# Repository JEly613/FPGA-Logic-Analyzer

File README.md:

### See sims/ For Current Progress

## Concept:

Logic analyzer & oscilloscope with 4 digital channels and 2 analog channels processed with the Cmod A7 35-T FPGA board. The board uses a UART-USB bridge so the streaming rate is highly limited. 

The solution is to write incoming data to SRAM then slowly read it all off, giving a snapshot of input signal. Goal is to do this at 100MHz for digital input.

Currently designing analog front end for digital and analog channels. See sims and calculations for more details.

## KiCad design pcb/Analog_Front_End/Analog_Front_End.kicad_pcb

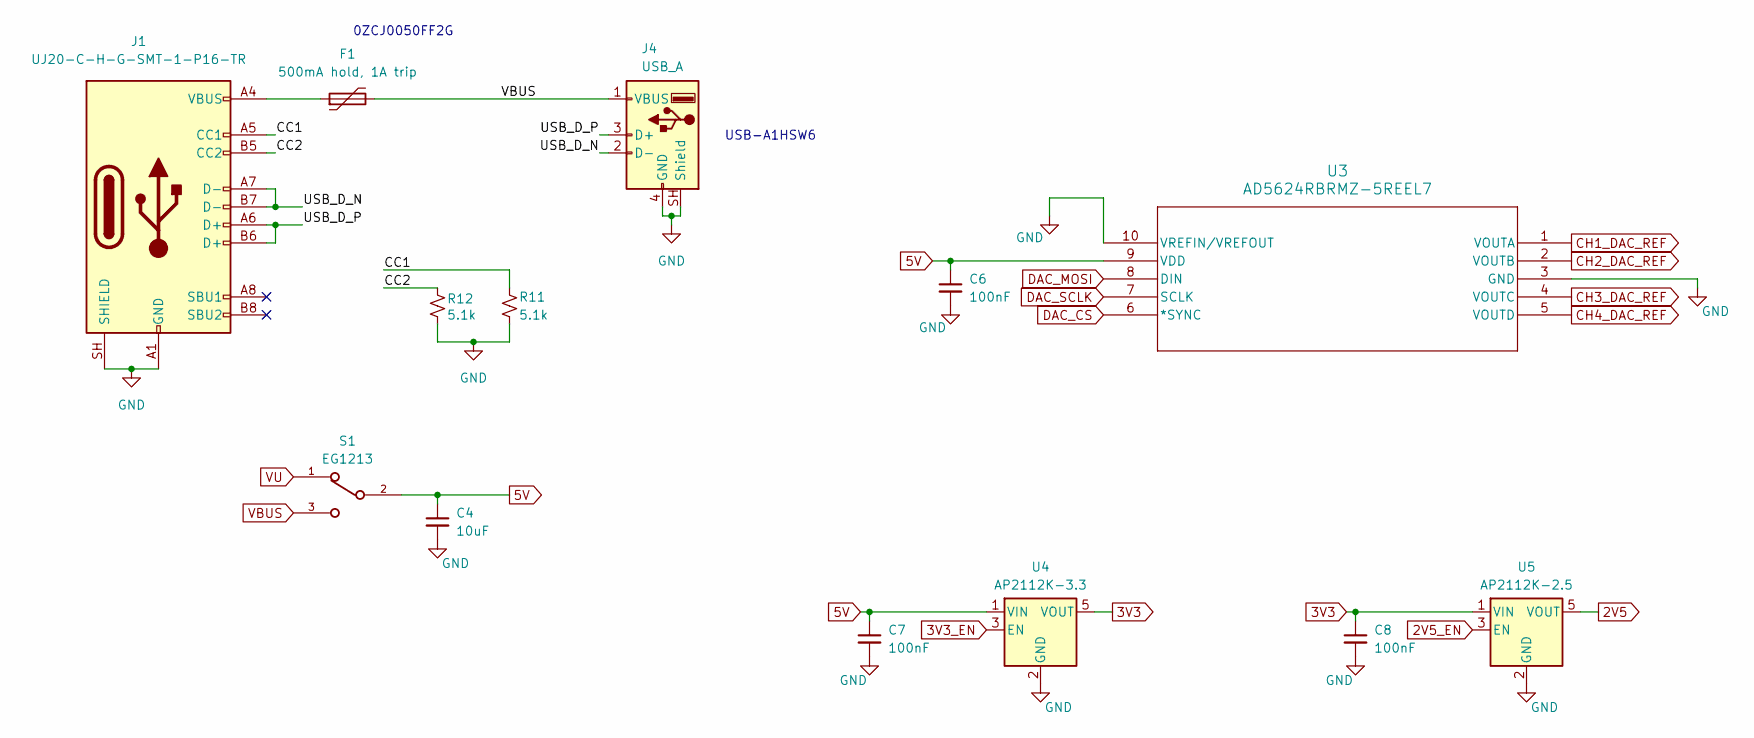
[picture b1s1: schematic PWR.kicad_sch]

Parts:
C4: 10uF; C_0603_1608Metric_Pad1.08x0.95mm_HandSolder
C6, C7, C8: 100nF; C_0603_1608Metric_Pad1.08x0.95mm_HandSolder
F1: 500mA hold, 1A trip; Fuse_1206_3216Metric_Pad1.42x1.75mm_HandSolder
J1: UJ20-C-H-G-SMT-1-P16-TR; SAMESKY_UJ20-C-H-G-SMT-1-P16-TR
J4: USB_A; CONN_USB-A1HSW6_OST
R11, R12: 5.1k; R_0603_1608Metric_Pad0.98x0.95mm_HandSolder
S1: EG1213; SW_EG1213; DigiKey_Part_Number EG1906-ND
U3: AD5624RBRMZ-5REEL7; RM_10_ADI-L
U4: AP2112K-3.3; SOT-23-5
U5: AP2112K-2.5; SOT-23-5

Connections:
2V5: U5.5 (VOUT); also elsewhere on the board
2V5_EN: U5.3 (EN); also elsewhere on the board
3V3: C8.1, U4.5 (VOUT), U5.1 (VIN); also elsewhere on the board
3V3_EN: U4.3 (EN); also elsewhere on the board
5V: C4.1, C6.1, C7.1, S1.2, U3.9 (VDD), U4.1 (VIN); also elsewhere on the board
/PWR/CC1: J1.A5 (CC1), R11.2
/PWR/CC2: J1.B5 (CC2), R12.2
/PWR/USB_D_N: J1.A7 (D-), J1.B7 (D-), J4.2 (D-)
/PWR/USB_D_P: J1.A6 (D+), J1.B6 (D+), J4.3 (D+)
CH1_DAC_REF: U3.1 (VOUTA); also elsewhere on the board
CH2_DAC_REF: U3.2 (VOUTB); also elsewhere on the board
CH3_DAC_REF: U3.4 (VOUTC); also elsewhere on the board
CH4_DAC_REF: U3.5 (VOUTD); also elsewhere on the board
DAC_CS: U3.6 (*SYNC); also elsewhere on the board
DAC_MOSI: U3.8 (DIN); also elsewhere on the board
DAC_SCLK: U3.7 (SCLK); also elsewhere on the board
GND: C4.2, C6.2, C7.2, C8.2, J1.A1 (GND), J1.A12 (GND), J1.B1 (GND), J1.B12 (GND), J1.SH (SHIELD), J4.4 (GND), J4.SH (Shield), R11.1, R12.1, U3.3 (GND), U3.10 (VREFIN/VREFOUT), U4.2 (GND), U5.2 (GND); also elsewhere on the board
unnamed: F1.1, J1.A4 (VBUS), J1.A9 (VBUS), J1.B4 (VBUS), J1.B9 (VBUS)
VBUS: F1.2, J4.1 (VBUS), S1.3
VU: S1.1; also elsewhere on the board

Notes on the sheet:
0ZCJ0050FF2G
USB-A1HSW6

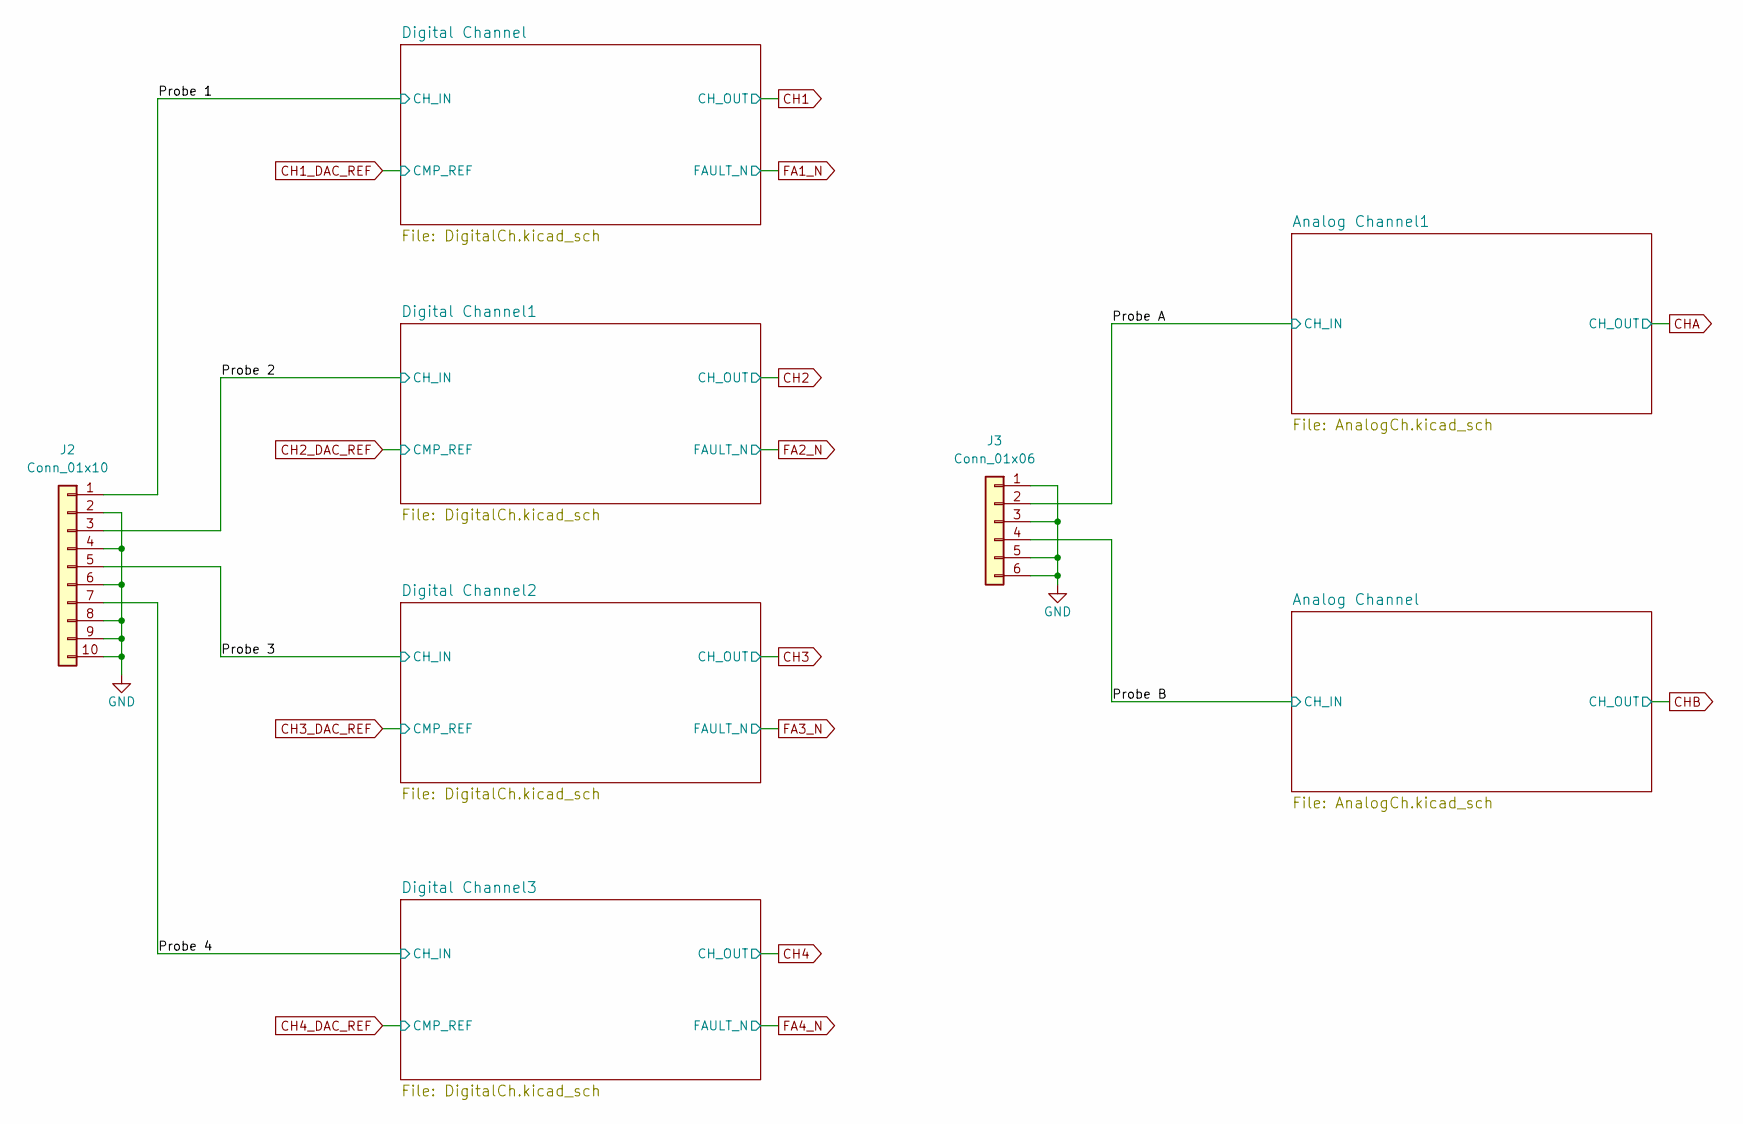
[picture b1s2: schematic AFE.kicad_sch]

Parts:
J2: Conn_01x10; BoxHeader_2x05_P2.54mm_Horizontal
J3: Conn_01x06; BoxHeader_2x03_P2.54mm_Horizontal

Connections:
/AFE/Probe 1: J2.1; also elsewhere on the board
/AFE/Probe 2: J2.3; also elsewhere on the board
/AFE/Probe 3: J2.5; also elsewhere on the board
/AFE/Probe 4: J2.7; also elsewhere on the board
/AFE/Probe A: J3.2; also elsewhere on the board
/AFE/Probe B: J3.4; also elsewhere on the board
GND: J2.2, J2.4, J2.6, J2.8, J2.9, J2.10, J3.1, J3.3, J3.5, J3.6; also elsewhere on the board

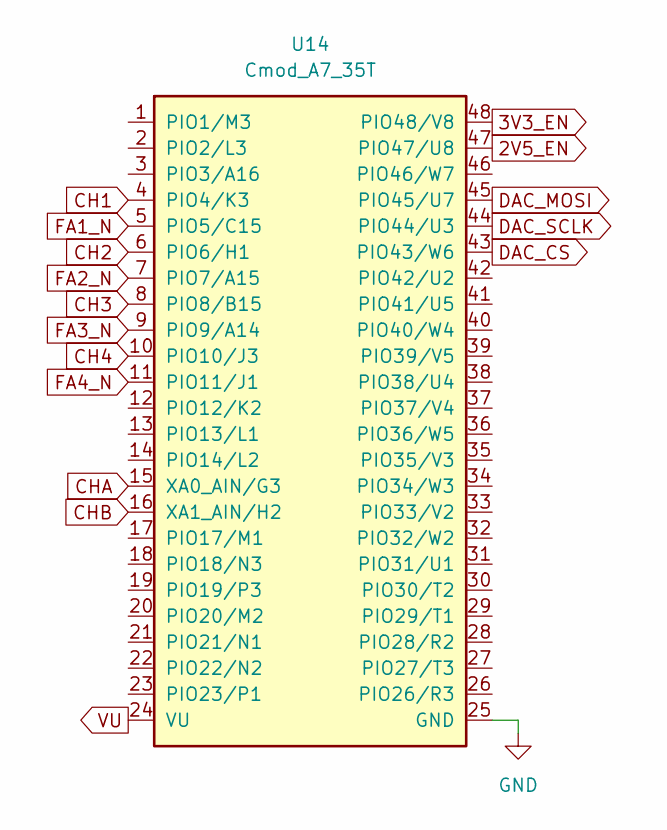
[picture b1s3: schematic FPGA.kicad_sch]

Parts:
U14: Cmod_A7_35T; Cmod_A7_DIP48_W15.24mm_Socket; MPN 410-328-35

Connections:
2V5_EN: U14.47 (PIO47/U8); also elsewhere on the board
3V3_EN: U14.48 (PIO48/V8); also elsewhere on the board
CH1: U14.4 (PIO4/K3); also elsewhere on the board
CH2: U14.6 (PIO6/H1); also elsewhere on the board
CH3: U14.8 (PIO8/B15); also elsewhere on the board
CH4: U14.10 (PIO10/J3); also elsewhere on the board
CHA: U14.15 (XA0_AIN/G3); also elsewhere on the board
CHB: U14.16 (XA1_AIN/H2); also elsewhere on the board
DAC_CS: U14.43 (PIO43/W6); also elsewhere on the board
DAC_MOSI: U14.45 (PIO45/U7); also elsewhere on the board
DAC_SCLK: U14.44 (PIO44/U3); also elsewhere on the board
FA1_N: U14.5 (PIO5/C15); also elsewhere on the board
FA2_N: U14.7 (PIO7/A15); also elsewhere on the board
FA3_N: U14.9 (PIO9/A14); also elsewhere on the board
FA4_N: U14.11 (PIO11/J1); also elsewhere on the board
GND: U14.25 (GND); also elsewhere on the board
VU: U14.24 (VU); also elsewhere on the board

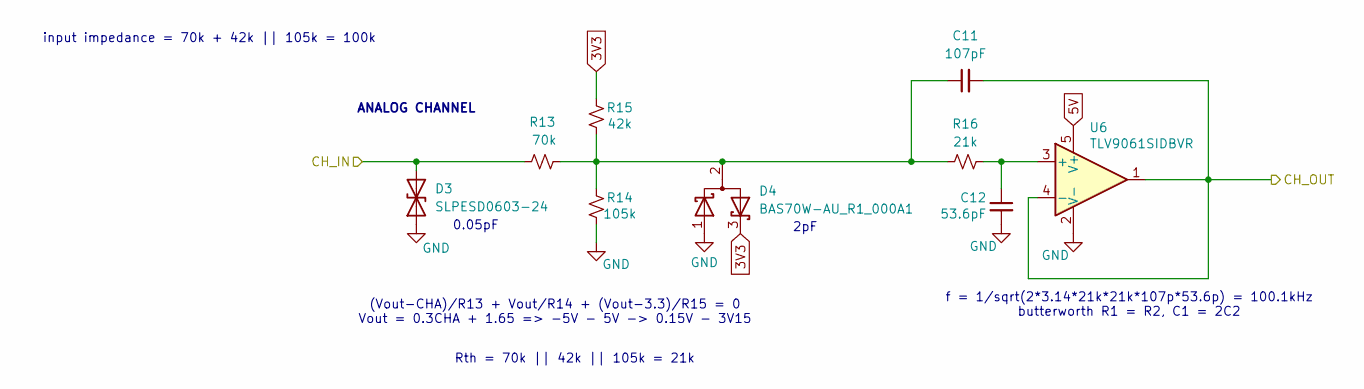
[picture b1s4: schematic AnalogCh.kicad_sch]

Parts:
C11: 107pF; C_0603_1608Metric_Pad1.08x0.95mm_HandSolder
C12: 53.6pF; C_0603_1608Metric_Pad1.08x0.95mm_HandSolder
D3: SLPESD0603-24; D_0603_1608Metric_Pad1.05x0.95mm_HandSolder
D4: BAS70W-AU_R1_000A1; SOT-323_SC-70
R13: 70k; R_0603_1608Metric_Pad0.98x0.95mm_HandSolder
R14: 105k; R_0603_1608Metric_Pad0.98x0.95mm_HandSolder
R15: 42k; R_0603_1608Metric_Pad0.98x0.95mm_HandSolder
R16: 21k; R_0603_1608Metric_Pad0.98x0.95mm_HandSolder
U6: TLV9061SIDBVR; SOT-23-5

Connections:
3V3: D4.3 (K), R15.1; also elsewhere on the board
5V: U6.5 (V+); also elsewhere on the board
/AFE/Probe B: D3.2 (A2), R13.1; also elsewhere on the board
CHB: C11.2, U6.1, U6.4 (-); also elsewhere on the board
GND: C12.2, D3.1 (A1), D4.1 (K), R14.2, U6.2 (V-); also elsewhere on the board
unnamed: C11.1, D4.2 (A), R13.2, R14.1, R15.2, R16.1
unnamed: C12.1, R16.2, U6.3 (+)

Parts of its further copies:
C23: 107pF; C_0603_1608Metric_Pad1.08x0.95mm_HandSolder
C24: 53.6pF; C_0603_1608Metric_Pad1.08x0.95mm_HandSolder
D11: SLPESD0603-24; D_0603_1608Metric_Pad1.05x0.95mm_HandSolder
D12: BAS70W-AU_R1_000A1; SOT-323_SC-70
R47: 70k; R_0603_1608Metric_Pad0.98x0.95mm_HandSolder
R48: 42k; R_0603_1608Metric_Pad0.98x0.95mm_HandSolder
R49: 105k; R_0603_1608Metric_Pad0.98x0.95mm_HandSolder
R50: 21k; R_0603_1608Metric_Pad0.98x0.95mm_HandSolder
U13: TLV9061SIDBVR; SOT-23-5

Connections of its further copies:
3V3: D12.3 (K), R48.1; also elsewhere on the board
5V: U13.5 (V+); also elsewhere on the board
/AFE/Probe A: D11.2 (A2), R47.1; also elsewhere on the board
CHA: C23.2, U13.1, U13.4 (-); also elsewhere on the board
GND: C24.2, D11.1 (A1), D12.1 (K), R49.2, U13.2 (V-); also elsewhere on the board
unnamed: C23.1, D12.2 (A), R47.2, R48.2, R49.1, R50.1
unnamed: C24.1, R50.2, U13.3 (+)

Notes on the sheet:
Rth = 70k || 42k || 105k = 21k
ANALOG CHANNEL
2pF
0.05pF
f = 1/sqrt(2*3.14*21k*21k*107p*53.6p) = 100.1kHz butterworth R1 = R2, C1 = 2C2
(Vout-CHA)/R13 + Vout/R14 + (Vout-3.3)/R15 = 0 Vout = 0.3CHA + 1.65 => -5V - 5V -> 0.15V - 3V15
input impedance = 70k + 42k || 105k = 100k

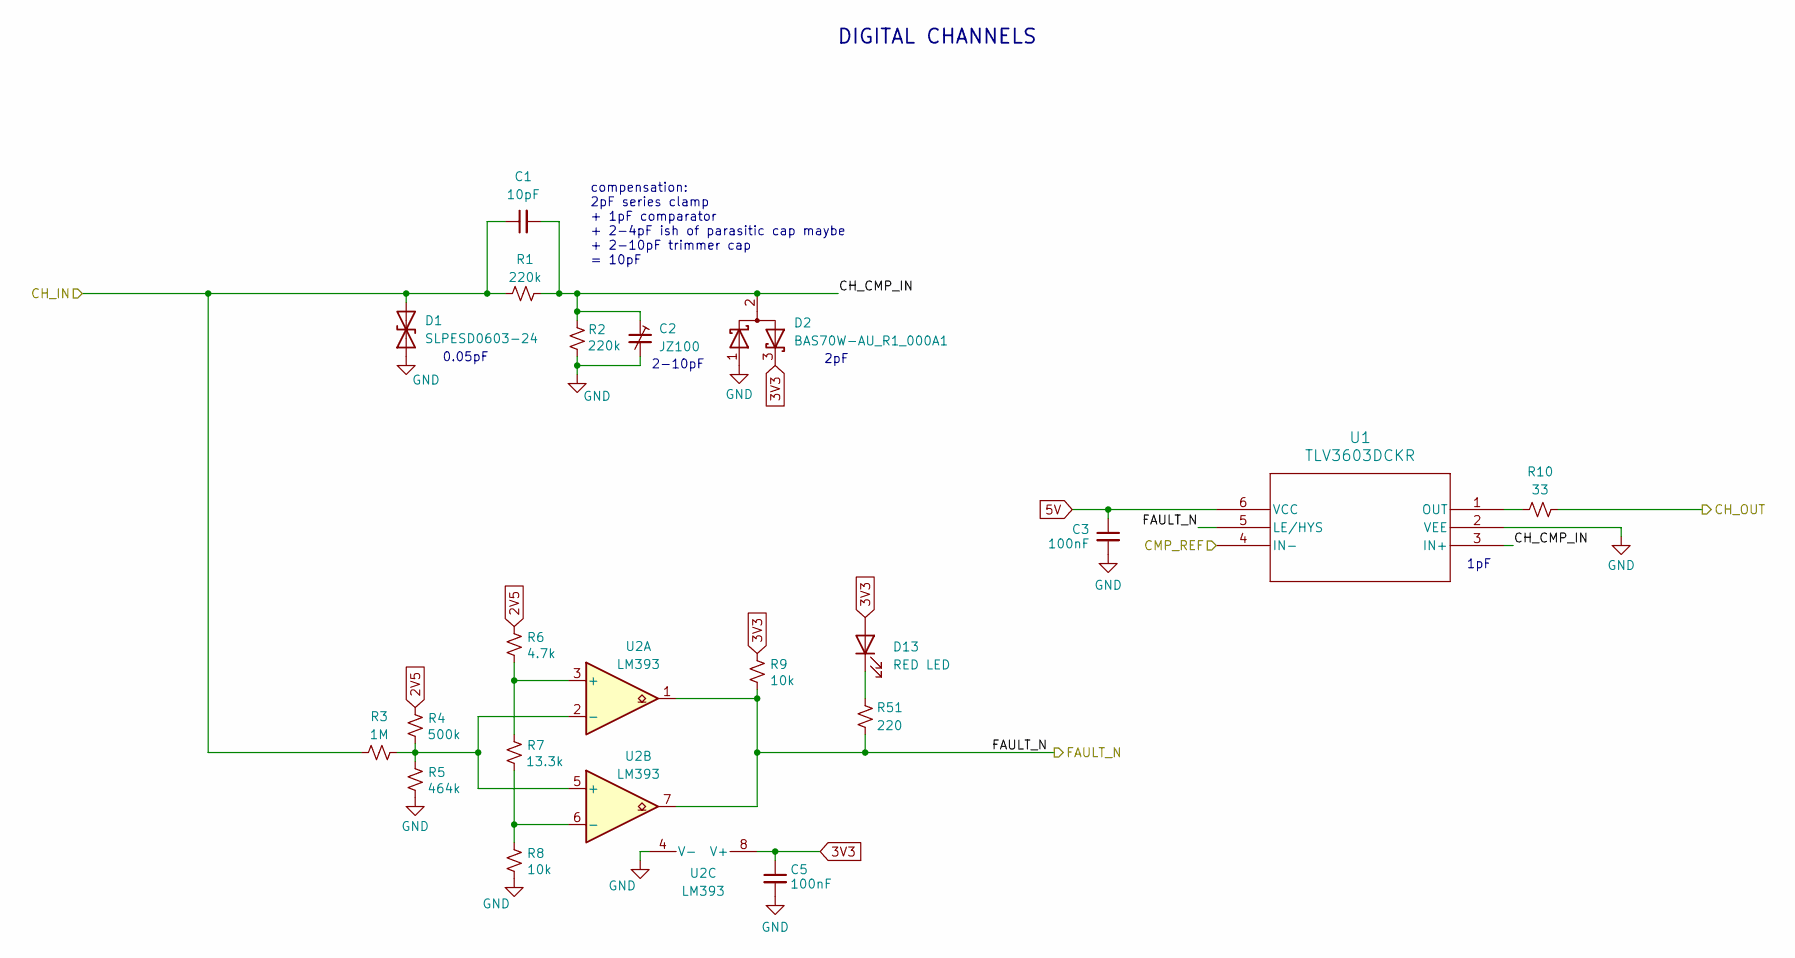
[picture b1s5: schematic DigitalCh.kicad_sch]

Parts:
C1: 10pF; C_0603_1608Metric_Pad1.08x0.95mm_HandSolder
C2: JZ100; C_0603_1608Metric_Pad1.08x0.95mm_HandSolder
C3, C5: 100nF; C_0603_1608Metric_Pad1.08x0.95mm_HandSolder
D1: SLPESD0603-24; D_0603_1608Metric_Pad1.05x0.95mm_HandSolder
D2: BAS70W-AU_R1_000A1; SOT-323_SC-70
D13: RED LED; LED_0805_2012Metric_Pad1.15x1.40mm_HandSolder
R1, R2: 220k; R_0603_1608Metric_Pad0.98x0.95mm_HandSolder
R3: 1M; R_0603_1608Metric_Pad0.98x0.95mm_HandSolder
R4: 500k; R_0603_1608Metric_Pad0.98x0.95mm_HandSolder
R5: 464k; R_0603_1608Metric_Pad0.98x0.95mm_HandSolder
R6: 4.7k; R_0603_1608Metric_Pad0.98x0.95mm_HandSolder
R7: 13.3k; R_0603_1608Metric_Pad0.98x0.95mm_HandSolder
R8, R9: 10k; R_0603_1608Metric_Pad0.98x0.95mm_HandSolder
R10: 33; R_0603_1608Metric_Pad0.98x0.95mm_HandSolder
R51: 220; R_0603_1608Metric_Pad0.98x0.95mm_HandSolder
U1: TLV3603DCKR; SC70_DCK_TEX
U2: LM393; LM393-L

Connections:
2V5: R4.1, R6.1; also elsewhere on the board
3V3: C5.1, D2.3 (K), D13.2 (A), R9.1, U2.8 (V+); also elsewhere on the board
5V: C3.1, U1.6 (VCC); also elsewhere on the board
/AFE/Digital Channel/CH_CMP_IN: C1.2, C2.1, D2.2 (A), R1.2, R2.1, U1.3 (IN+)
/AFE/Probe 1: C1.1, D1.2 (A2), R1.1, R3.1; also elsewhere on the board
CH1: R10.2; also elsewhere on the board
CH1_DAC_REF: U1.4 (IN-); also elsewhere on the board
FA1_N: R9.2, R51.2, U1.5 (LE/HYS), U2.1, U2.7; also elsewhere on the board
GND: C2.2, C3.2, C5.2, D1.1 (A1), D2.1 (K), R2.2, R5.2, R8.2, U1.2 (VEE), U2.4 (V-); also elsewhere on the board
unnamed: D13.1 (K), R51.1
unnamed: R10.1, U1.1 (OUT)
unnamed: R6.2, R7.1, U2.3 (+)
unnamed: R3.2, R4.2, R5.1, U2.2 (-), U2.5 (+)
unnamed: R7.2, R8.1, U2.6 (-)

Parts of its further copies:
C9, C15, C19: 10pF; C_0603_1608Metric_Pad1.08x0.95mm_HandSolder
C10, C16, C20: JZ100; C_0603_1608Metric_Pad1.08x0.95mm_HandSolder
C13, C14, C17, C18, C21, C22: 100nF; C_0603_1608Metric_Pad1.08x0.95mm_HandSolder
D5, D7, D9: SLPESD0603-24; D_0603_1608Metric_Pad1.05x0.95mm_HandSolder
D6, D8, D10: BAS70W-AU_R1_000A1; SOT-323_SC-70
D14, D15, D16: RED LED; LED_0805_2012Metric_Pad1.15x1.40mm_HandSolder
R17, R27, R37: 1M; R_0603_1608Metric_Pad0.98x0.95mm_HandSolder
R18, R28, R38: 500k; R_0603_1608Metric_Pad0.98x0.95mm_HandSolder
R19, R29, R39: 464k; R_0603_1608Metric_Pad0.98x0.95mm_HandSolder
R20, R30, R40: 4.7k; R_0603_1608Metric_Pad0.98x0.95mm_HandSolder
R21, R31, R41: 13.3k; R_0603_1608Metric_Pad0.98x0.95mm_HandSolder
R22, R25, R32, R35, R42, R45: 10k; R_0603_1608Metric_Pad0.98x0.95mm_HandSolder
R23, R24, R33, R34, R43, R44: 220k; R_0603_1608Metric_Pad0.98x0.95mm_HandSolder
R26, R36, R46: 33; R_0603_1608Metric_Pad0.98x0.95mm_HandSolder
R52, R53, R54: 220; R_0603_1608Metric_Pad0.98x0.95mm_HandSolder
U7, U9, U11: LM393; LM393-L
U8, U10, U12: TLV3603DCKR; SC70_DCK_TEX

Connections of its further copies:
2V5: R18.1, R20.1, R28.1, R30.1, R38.1, R40.1; also elsewhere on the board
3V3: C13.1, C17.1, C21.1, D6.3 (K), D8.3 (K), D10.3 (K), D14.2 (A), D15.2 (A), D16.2 (A), R25.1, R35.1, R45.1, U7.8 (V+), U9.8 (V+), U11.8 (V+); also elsewhere on the board
5V: C14.1, C18.1, C22.1, U8.6 (VCC), U10.6 (VCC), U12.6 (VCC); also elsewhere on the board
/AFE/Digital Channel1/CH_CMP_IN: C9.2, C10.1, D6.2 (A), R23.2, R24.1, U8.3 (IN+)
/AFE/Digital Channel2/CH_CMP_IN: C15.2, C16.1, D8.2 (A), R33.2, R34.1, U10.3 (IN+)
/AFE/Digital Channel3/CH_CMP_IN: C19.2, C20.1, D10.2 (A), R43.2, R44.1, U12.3 (IN+)
/AFE/Probe 2: C9.1, D5.2 (A2), R17.1, R23.1; also elsewhere on the board
/AFE/Probe 3: C15.1, D7.2 (A2), R27.1, R33.1; also elsewhere on the board
/AFE/Probe 4: C19.1, D9.2 (A2), R37.1, R43.1; also elsewhere on the board
CH2: R26.2; also elsewhere on the board
CH2_DAC_REF: U8.4 (IN-); also elsewhere on the board
CH3: R36.2; also elsewhere on the board
CH3_DAC_REF: U10.4 (IN-); also elsewhere on the board
CH4: R46.2; also elsewhere on the board
CH4_DAC_REF: U12.4 (IN-); also elsewhere on the board
FA2_N: R25.2, R52.2, U7.1, U7.7, U8.5 (LE/HYS); also elsewhere on the board
FA3_N: R35.2, R53.2, U9.1, U9.7, U10.5 (LE/HYS); also elsewhere on the board
FA4_N: R45.2, R54.2, U11.1, U11.7, U12.5 (LE/HYS); also elsewhere on the board
GND: C10.2, C13.2, C14.2, C16.2, C17.2, C18.2, C20.2, C21.2, C22.2, D5.1 (A1), D6.1 (K), D7.1 (A1), D8.1 (K), D9.1 (A1), D10.1 (K), R19.2, R22.2, R24.2, R29.2, R32.2, R34.2, R39.2, R42.2, R44.2, U7.4 (V-), U8.2 (VEE), U9.4 (V-), U10.2 (VEE), U11.4 (V-), U12.2 (VEE); also elsewhere on the board
unnamed: D14.1 (K), R52.1
unnamed: D15.1 (K), R53.1
unnamed: D16.1 (K), R54.1
unnamed: R20.2, R21.1, U7.3 (+)
unnamed: R17.2, R18.2, R19.1, U7.2 (-), U7.5 (+)
unnamed: R21.2, R22.1, U7.6 (-)
unnamed: R26.1, U8.1 (OUT)
unnamed: R30.2, R31.1, U9.3 (+)
unnamed: R27.2, R28.2, R29.1, U9.2 (-), U9.5 (+)
unnamed: R31.2, R32.1, U9.6 (-)
unnamed: R36.1, U10.1 (OUT)
unnamed: R40.2, R41.1, U11.3 (+)
unnamed: R37.2, R38.2, R39.1, U11.2 (-), U11.5 (+)
unnamed: R41.2, R42.1, U11.6 (-)
unnamed: R46.1, U12.1 (OUT)

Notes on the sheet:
1pF
0.05pF
2pF
DIGITAL CHANNELS
compensation: 2pF series clamp + 1pF comparator + 2-4pF ish of parasitic cap maybe + 2-10pF trimmer cap = 10pF
2-10pF

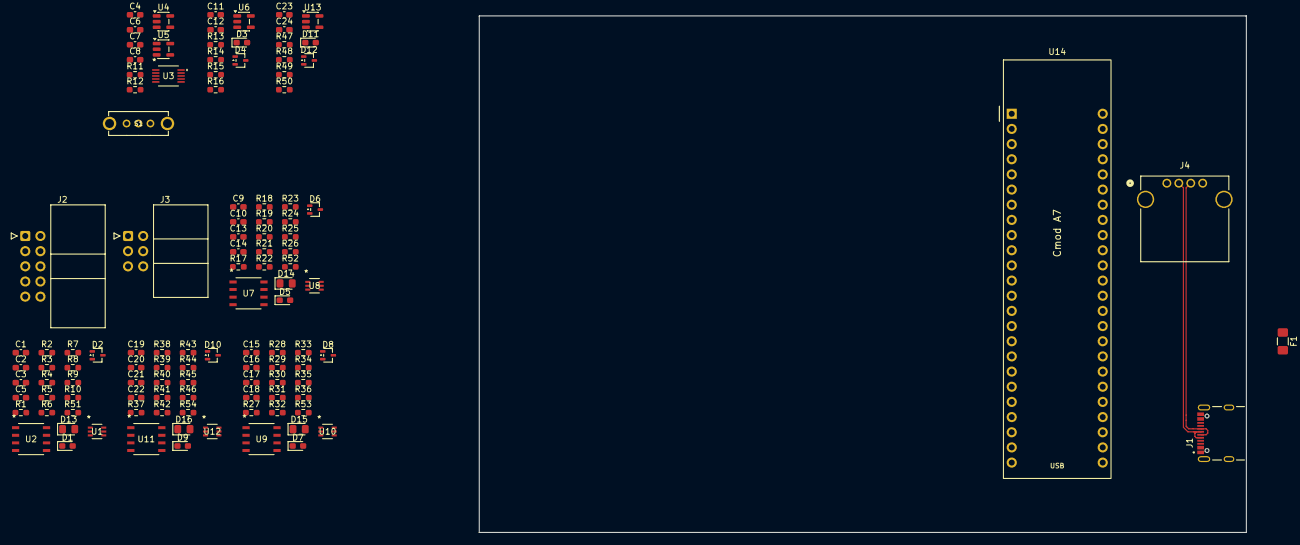
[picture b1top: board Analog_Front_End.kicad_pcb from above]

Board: 4 copper layers, 128.5 x 86.5 mm, 114 parts (0 on the bottom side), 64 nets.
